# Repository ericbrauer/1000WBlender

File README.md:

# 1000WBlender
A combination blend and feedback noise toy

## Schematic
Can be found in `assets/`

## Notes for Next Rev.

- Definitely want Linear Potentiometers for both FB and Blend.
- Both Blend and FB don't change much until the final 30% of the rotation. This
  could be played with.
- Input and Send on right side of pedal, Out and Return on left side.
- Tight Squeeze in the Enclosure!

## More Notes

- Dedicated Volume for FB?

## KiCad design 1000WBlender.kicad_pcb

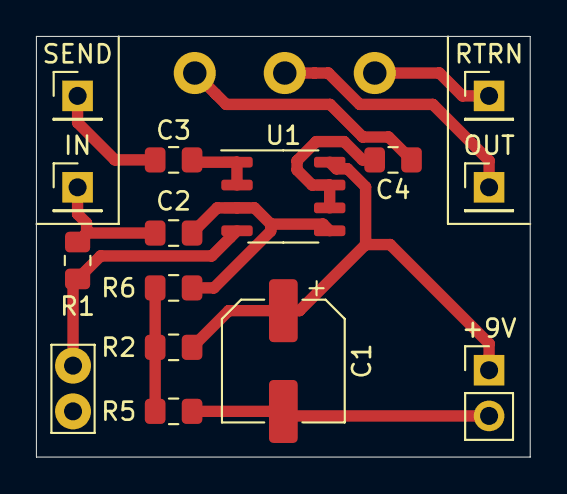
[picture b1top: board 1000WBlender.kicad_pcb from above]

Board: 2 copper layers, 27.4 x 23.4 mm, 15 parts (1 on the bottom side), 11 nets.

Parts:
+9V: Battery_Cell; PinHeader_1x02_P2.54mm_Vertical
C1: 100u; CP_Elec_6.3x5.4
C2, C3, C4: 100n; C_0805_2012Metric_Pad1.15x1.40mm_HandSolder
IN: Conn_01x02_Female; PinHeader_1x01_P2.54mm_Vertical
OUT: Conn_01x02_Female; PinHeader_1x01_P2.54mm_Vertical
R1: 2.2M; R_0805_2012Metric_Pad1.15x1.40mm_HandSolder
R2, R5: 100k; R_0805_2012Metric_Pad1.15x1.40mm_HandSolder
R6: 1M; R_0805_2012Metric_Pad1.15x1.40mm_HandSolder
RTRN: Conn_01x02_Female; PinHeader_1x01_P2.54mm_Vertical
RV1: 100k; Potentiometer_Omeg_PC16BU_Vertical
SEND: Conn_01x02_Female; PinHeader_1x01_P2.54mm_Vertical
U1: TL072; SO-8_3.9x4.9mm_P1.27mm

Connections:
+4.5V: R2.2, R5.1, R6.1
+9V: +9V.1, C1.1, R2.1, U1.8
GND: +9V.2, C1.2, R1.2, R5.2, U1.4
IN: C2.2, IN.1, R1.1
unnamed: C2.1, R6.2, U1.3, U1.5
unnamed: C3.2, U1.1, U1.2
unnamed: C4.1, RV1.3
unnamed: C4.2, U1.6, U1.7
OUT: OUT.1, RV1.2
RTRN: RTRN.1, RV1.1
SEND: C3.1, SEND.1

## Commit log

2019-07-05 initial schematic
2019-07-05 added schematic and datasheet
2019-07-05 minor fixes
2019-07-26 some changes based on experimentation.
2019-08-02 notes made in readme
2019-08-02 notes made in readme II
2019-08-04 more README notes after weekend
2019-08-05 further comments
2019-08-06 changes made to schematic
2019-08-06 added. 4.5V symbol
2019-08-06 added complete symbol library
2019-08-06 new schematic.pdf
2019-08-06 added svg
2019-08-09 initial association of footprints VERIFY
2019-08-10 inital pcb layout WIP
2019-08-13 initial pcb placement
2019-08-16 update page settings
2019-08-18 work on pcb design
2019-08-18 routing done, gerbers exported, rev2 complete
2019-08-18 added render file
2019-09-11 fixing kicad_pcb file to work with kicad 5.1 as opposed to nightly
